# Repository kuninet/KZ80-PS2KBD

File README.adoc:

= KZ80マイコン用 MSX互換 PS/2キーボードアダプタ = 

== 概要 ==
* PS/2キーボードのシリアル信号をATMega328P AVRマイコンでMSX互換のPPI(8255)へつなげるボードです。
** PS/2キーボードのシリアル信号をATmega328Pの外部割り込み機能で受信
** AVRマイコン内部でMSXがおこなっているPPI(8255) Cポートのスキャン信号をもとにポート変化割り込み変化割り込みが届いた場合に、PPI(8255)Bポートへスキャンコードを出力します。

image::image/KZ80-PS2KBD.jpg[]

== 注意 ==
* **REV1基板には74HC00の電源が逆接続という重大なバグがあります。REV2をお待ち下さい。**
** 74HC00の電源ピンが逆なので、ICソケット2段などで工夫して配線修正してください。 

== ライセンスについて
* 私が作成した回路、プログラム(改修部分)等についてはMITライセンスで公開します。
* オリジナルとなったプログラムコード部分は以下のMSX Hobby氏に帰属します。
* PS/2キーボードのフットプリントはAgilack氏の成果を使わせていただきました。ライセンスはCC-by-SAです。

=== 参考・使用させていただいた情報
* mini DINパーツのフットプリント
** https://github.com/Agilack/contrib-kicad_parts
* ArduinoMEGAでPS/2キーボードをMSXへ(MSX Hobby)
** http://msx.gouget.com.br/2014/06/24/ps2-keyboard-to-msx-with-arduino/
* Custom KiCad Libraries
** https://github.com/4x1md/kicad_libraries

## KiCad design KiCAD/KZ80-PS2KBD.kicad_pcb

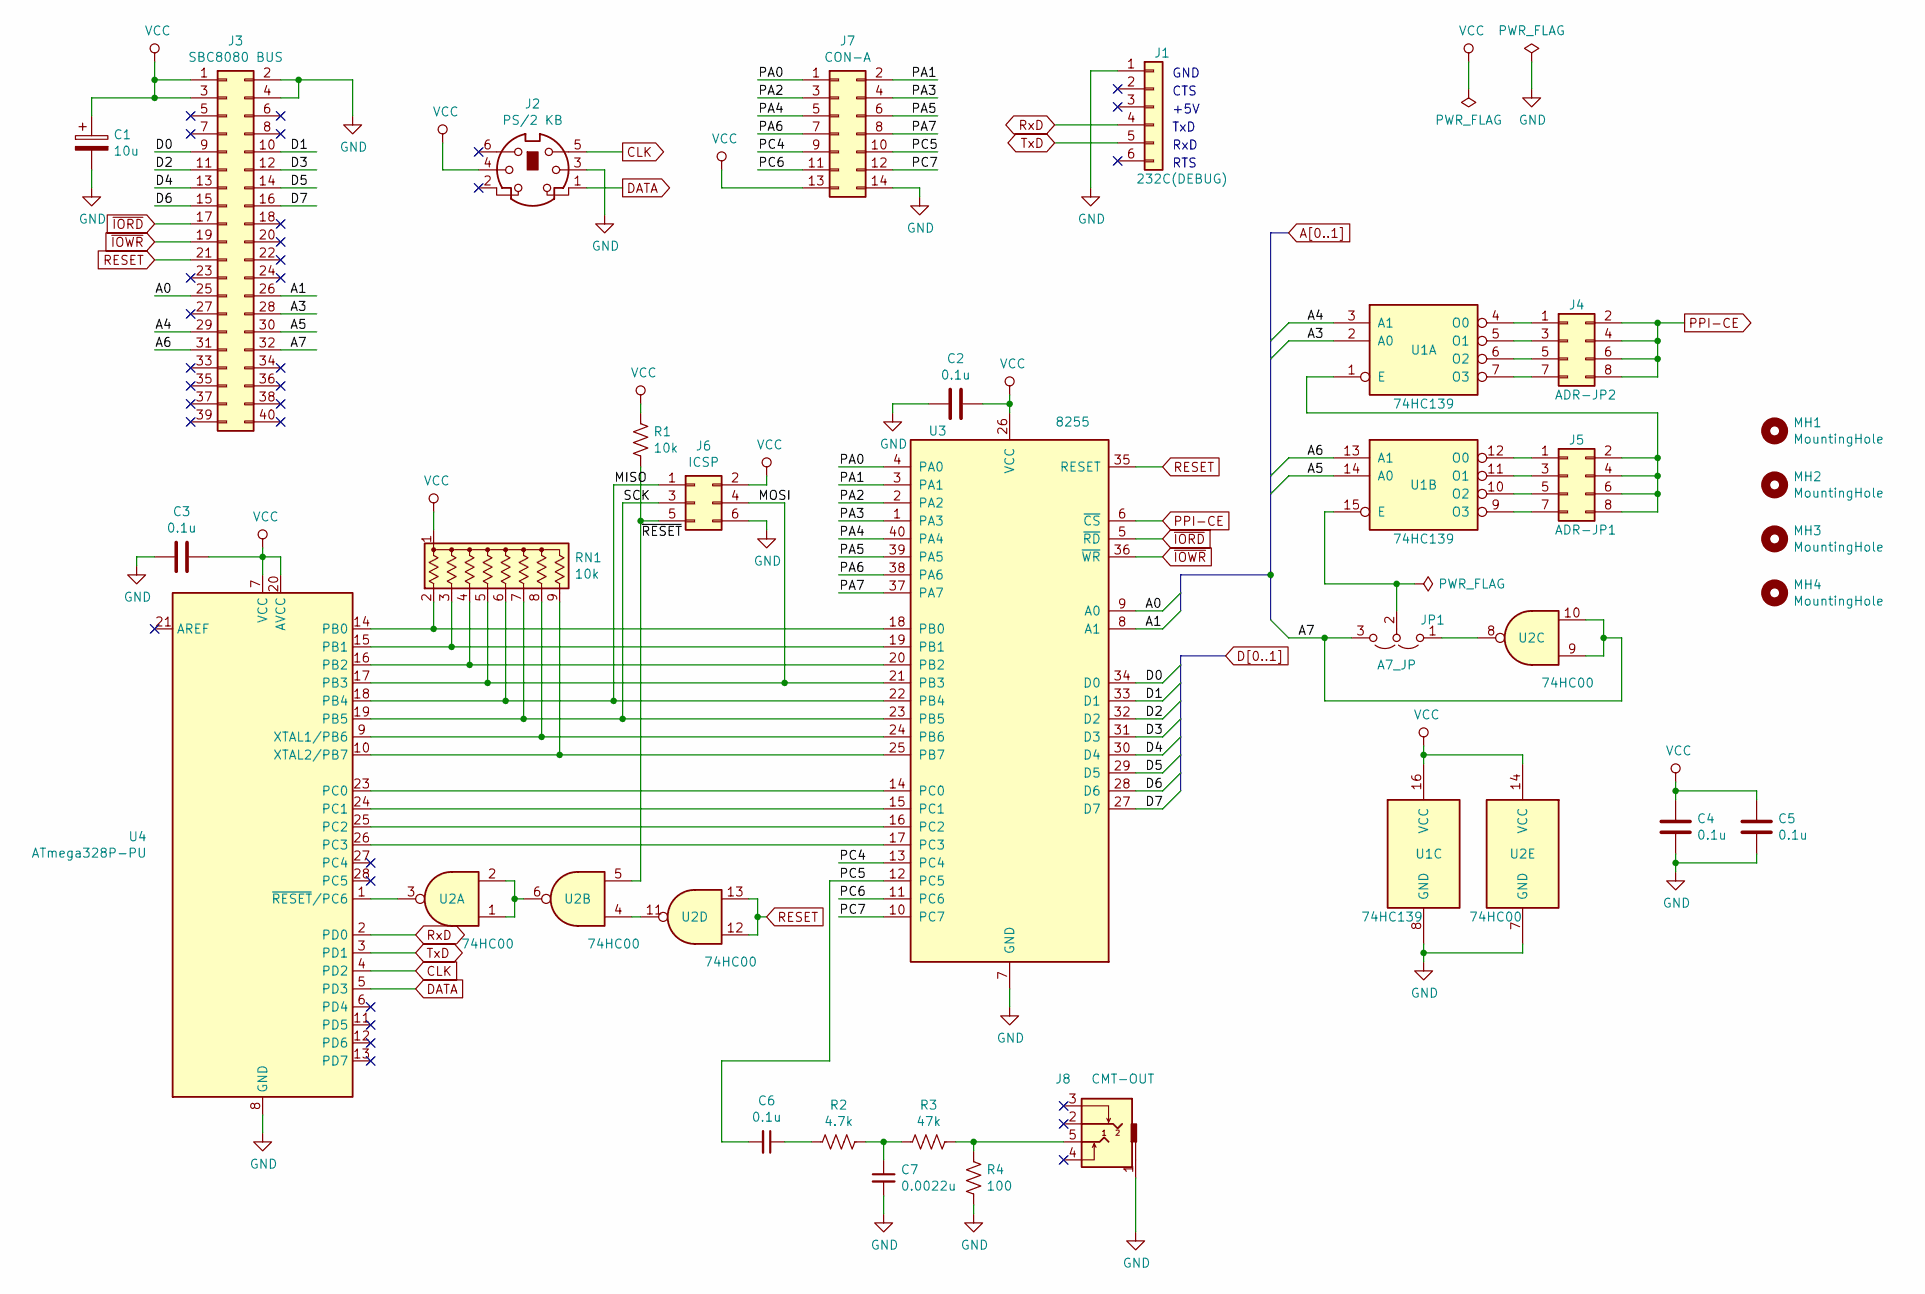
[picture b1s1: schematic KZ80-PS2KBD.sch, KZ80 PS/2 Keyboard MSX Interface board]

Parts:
C1: 10u; CP_Radial_D5.0mm_P2.50mm
C2, C3, C4, C5, C6: 0.1u; C_Disc_D3.0mm_W1.6mm_P2.50mm
C7: 0.0022u; C_Disc_D3.0mm_W1.6mm_P2.50mm
J1: 232C(DEBUG); PinHeader_1x06_P2.54mm_Horizontal
J2: PS/2 KB; din6-schurter-4850261
J3: SBC8080 BUS; PinHeader_2x20_P2.54mm_Horizontal
J4: ADR-JP2; PinHeader_2x04_P2.54mm_Vertical
J5: ADR-JP1; PinHeader_2x04_P2.54mm_Vertical
J6: ICSP; PinHeader_2x03_P2.54mm_Vertical
J7: CON-A; PinHeader_2x07_P2.54mm_Vertical
J8: CMT-OUT; AJ-1780
JP1: A7_JP; PinHeader_1x03_P2.54mm_Vertical
MH1, MH2, MH3, MH4: MountingHole; MountingHole_3.2mm_M3
R1: 10k; R_Axial_DIN0207_L6.3mm_D2.5mm_P10.16mm_Horizontal
R2: 4.7k; R_Axial_DIN0207_L6.3mm_D2.5mm_P10.16mm_Horizontal
R3: 47k; R_Axial_DIN0207_L6.3mm_D2.5mm_P10.16mm_Horizontal
R4: 100; R_Axial_DIN0207_L6.3mm_D2.5mm_P10.16mm_Horizontal
RN1: 10k; R_Array_SIP9
U1: 74HC139; DIP-16_W7.62mm_Socket
U2: 74HC00; DIP-14_W7.62mm_Socket
U3: 8255; DIP-40_W15.24mm_Socket
U4: ATmega328P-PU; DIP-28_W7.62mm_Socket

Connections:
/A3: J3.28, U1.2 (A0)
/A4: J3.29, U1.3 (A1)
/A5: J3.30, U1.14 (A0)
/A6: J3.31, U1.13 (A1)
/A7: J3.32, JP1.3 (B), U2.9, U2.10
/D2: J3.11, U3.32 (D2)
/D3: J3.12, U3.31 (D3)
/D4: J3.13, U3.30 (D4)
/D5: J3.14, U3.29 (D5)
/D6: J3.15, U3.28 (D6)
/D7: J3.16, U3.27 (D7)
/MISO: J6.1, RN1.6 (R5), U3.22 (PB4), U4.18 (PB4)
/MOSI: J6.4, RN1.5 (R4), U3.21 (PB3), U4.17 (PB3)
/PA0: J7.1, U3.4 (PA0)
/PA1: J7.2, U3.3 (PA1)
/PA2: J7.3, U3.2 (PA2)
/PA3: J7.4, U3.1 (PA3)
/PA4: J7.5, U3.40 (PA4)
/PA5: J7.6, U3.39 (PA5)
/PA6: J7.7, U3.38 (PA6)
/PA7: J7.8, U3.37 (PA7)
/PC4: J7.9, U3.13 (PC4)
/PC5: C6.2, J7.10, U3.12 (PC5)
/PC6: J7.11, U3.11 (PC6)
/PC7: J7.12, U3.10 (PC7)
/SCK: J6.3, RN1.7 (R6), U3.23 (PB5), U4.19 (PB5)
/~RESET: J6.5, R1.2, U2.5
A0: J3.25, U3.9 (A0)
A1: J3.26, U3.8 (A1)
CLK: J2.5, U4.4 (PD2)
D0: J3.9, U3.34 (D0)
D1: J3.10, U3.33 (D1)
DATA: J2.1, U4.5 (PD3)
GND: C1.2, C2.1, C3.2, C4.2, C5.2, C7.2, J1.1, J2.3, J3.2, J3.4, J6.6, J7.14, J8.1, R4.2, U1.8 (GND), U2.7 (GND), U3.7 (GND), U4.8 (GND), U4.22 (GND)
unnamed: C6.1, R2.2
unnamed: C7.1, R2.1, R3.2
unnamed: J4.1, U1.4 (O0)
unnamed: J4.3, U1.5 (O1)
unnamed: J4.5, U1.6 (O2)
unnamed: J4.7, U1.7 (O3)
unnamed: J5.1, U1.12 (O0)
unnamed: J5.2, J5.4, J5.6, J5.8, U1.1 (E)
unnamed: J5.3, U1.11 (O1)
unnamed: J5.5, U1.10 (O2)
unnamed: J5.7, U1.9 (O3)
unnamed: J8.5, R3.1, R4.1
unnamed: JP1.1 (A), U2.8
unnamed: JP1.2 (C), U1.15 (E)
unnamed: RN1.2 (R1), U3.18 (PB0), U4.14 (PB0)
unnamed: RN1.3 (R2), U3.19 (PB1), U4.15 (PB1)
unnamed: RN1.4 (R3), U3.20 (PB2), U4.16 (PB2)
unnamed: RN1.8 (R7), U3.24 (PB6), U4.9 (XTAL1/PB6)
unnamed: RN1.9 (R8), U3.25 (PB7), U4.10 (XTAL2/PB7)
unnamed: U2.1, U2.2, U2.6
unnamed: U2.3, U4.1 (~RESET~/PC6)
unnamed: U2.4, U2.11
unnamed: U3.14 (PC0), U4.23 (PC0)
unnamed: U3.15 (PC1), U4.24 (PC1)
unnamed: U3.16 (PC2), U4.25 (PC2)
unnamed: U3.17 (PC3), U4.26 (PC3)
PPI-CE: J4.2, J4.4, J4.6, J4.8, U3.6 (~CS~)
RESET: J3.21, U2.12, U2.13, U3.35 (RESET)
RxD: J1.4, U4.2 (PD0)
TxD: J1.5, U4.3 (PD1)
VCC: C1.1, C2.2, C3.1, C4.1, C5.1, J2.4, J3.1, J3.3, J6.2, J7.13, R1.1, RN1.1 (common), U1.16 (VCC), U2.14 (VCC), U3.26 (VCC), U4.7 (VCC), U4.20 (AVCC)
~IORD: J3.17, U3.5 (~RD~)
~IOWR: J3.19, U3.36 (~WR~)

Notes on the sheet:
GND
RTS
+5V
RxD
TxD
CTS

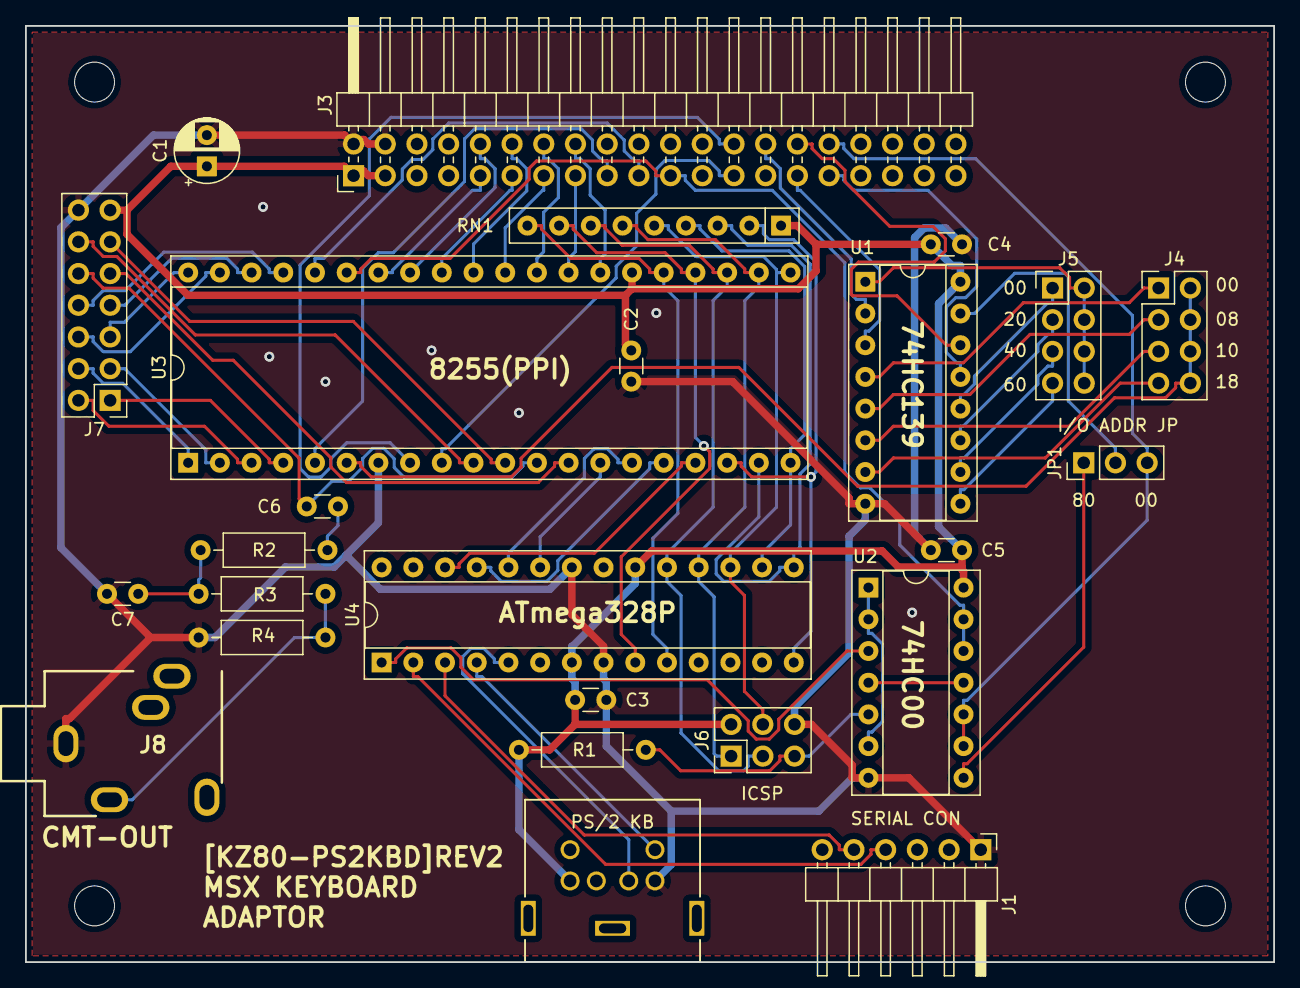
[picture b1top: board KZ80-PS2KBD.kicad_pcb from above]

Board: 2 copper layers, 100.0 x 75.0 mm, 29 parts (0 on the bottom side), 67 nets.

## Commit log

2019-10-06 init commit
2019-10-06 回路図イメージ作成
2019-12-21 REV1基板製造用ガーバーデータ出力版
2020-03-18 74HC00 Vcc-GND修正 ver 1.1へ
2020-03-18 74HC00 電源ピン配線見直しプリントパターン作成
2020-03-20 ボードコントール用ファームウェア追加
2020-03-22 MSXキースキャンの波形データを元にプログラム改良
2021-03-22 CMT出力回路追加・REV2基板ガーバー出力
2021-03-24 REV2基板 部品配置見直し・ガーバーデータ出力
2021-08-12 プリントパターン見直し・ガーバーデータ再出力
